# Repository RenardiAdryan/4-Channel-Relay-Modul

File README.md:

# 4-Channel-Relay-Modul
DIY Relay Modul

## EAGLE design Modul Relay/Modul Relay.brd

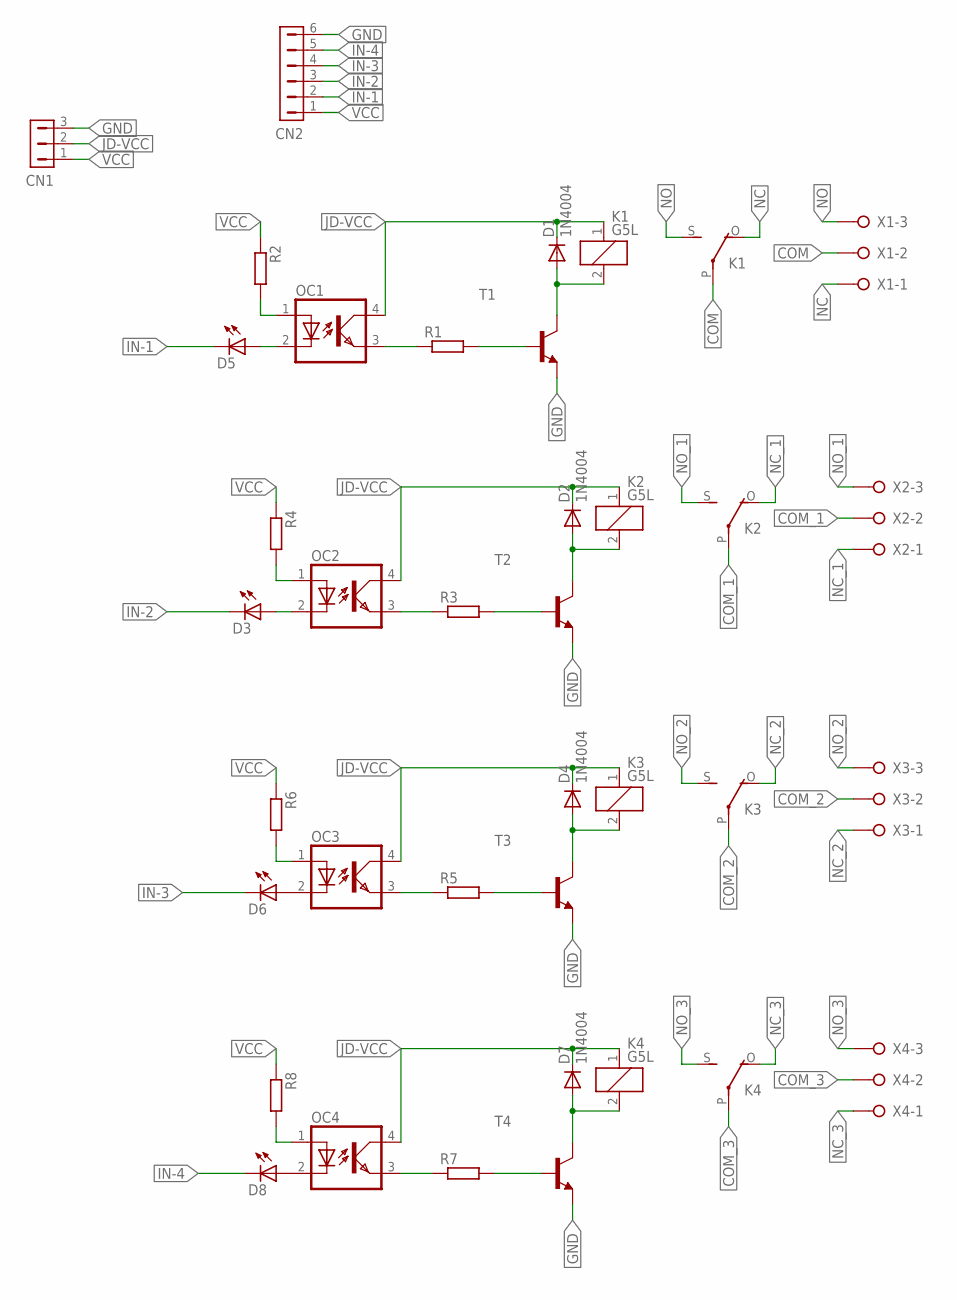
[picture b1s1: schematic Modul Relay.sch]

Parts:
CN1: HDR-1X3; SIP-100-3V
CN2: HDR-1X6-SIP-100; SIP-100-6V
D1, D2, D4, D7: 1N4004; DO41-10
D3, D5, D6, D8: LED3MM
K1, K2, K3, K4: G5L; G5LE
OC1, OC2, OC3, OC4: PC817; DIL04
R1, R2, R3, R4, R5, R6, R7, R8: R-EU_R0805; R0805
T1, T2, T3, T4: -NPN-TO92-ECB; TO92-ECB
X1, X2, X3, X4: W237-3E

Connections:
COM: K1.P, X1.2
COM_1: K2.P, X2.2
COM_2: K3.P, X3.2
COM_3: K4.P, X4.2
GND: CN1.3, CN2.6, T1.E, T2.E, T3.E, T4.E
IN-1: CN2.2, D5.K (C)
IN-2: CN2.3, D3.K (C)
IN-3: CN2.4, D6.K (C)
IN-4: CN2.5, D8.K (C)
JD-VCC: CN1.2, D1.C, D2.C, D4.C, D7.C, K1.1, K2.1, K3.1, K4.1, OC1.4 (COL), OC2.4 (COL), OC3.4 (COL), OC4.4 (COL)
unnamed: D2.A, K2.2, T2.C
unnamed: D1.A, K1.2, T1.C
unnamed: OC1.1 (A), R2.2
unnamed: R3.2, T2.B
unnamed: OC2.3 (EMIT), R3.1
unnamed: D3.A, OC2.2 (C)
unnamed: OC2.1 (A), R4.2
unnamed: D4.A, K3.2, T3.C
unnamed: R1.2, T1.B
unnamed: OC1.3 (EMIT), R1.1
unnamed: D5.A, OC1.2 (C)
unnamed: R5.2, T3.B
unnamed: OC3.3 (EMIT), R5.1
unnamed: D6.A, OC3.2 (C)
unnamed: OC3.1 (A), R6.2
unnamed: D7.A, K4.2, T4.C
unnamed: R7.2, T4.B
unnamed: OC4.3 (EMIT), R7.1
unnamed: D8.A, OC4.2 (C)
unnamed: OC4.1 (A), R8.2
NC: K1.O, X1.1
NC_1: K2.O, X2.1
NC_2: K3.O, X3.1
NC_3: K4.O, X4.1
NO: K1.S, X1.3
NO_1: K2.S, X2.3
NO_2: K3.S, X3.3
NO_3: K4.S, X4.3
VCC: CN1.1, CN2.1, R2.1, R4.1, R6.1, R8.1

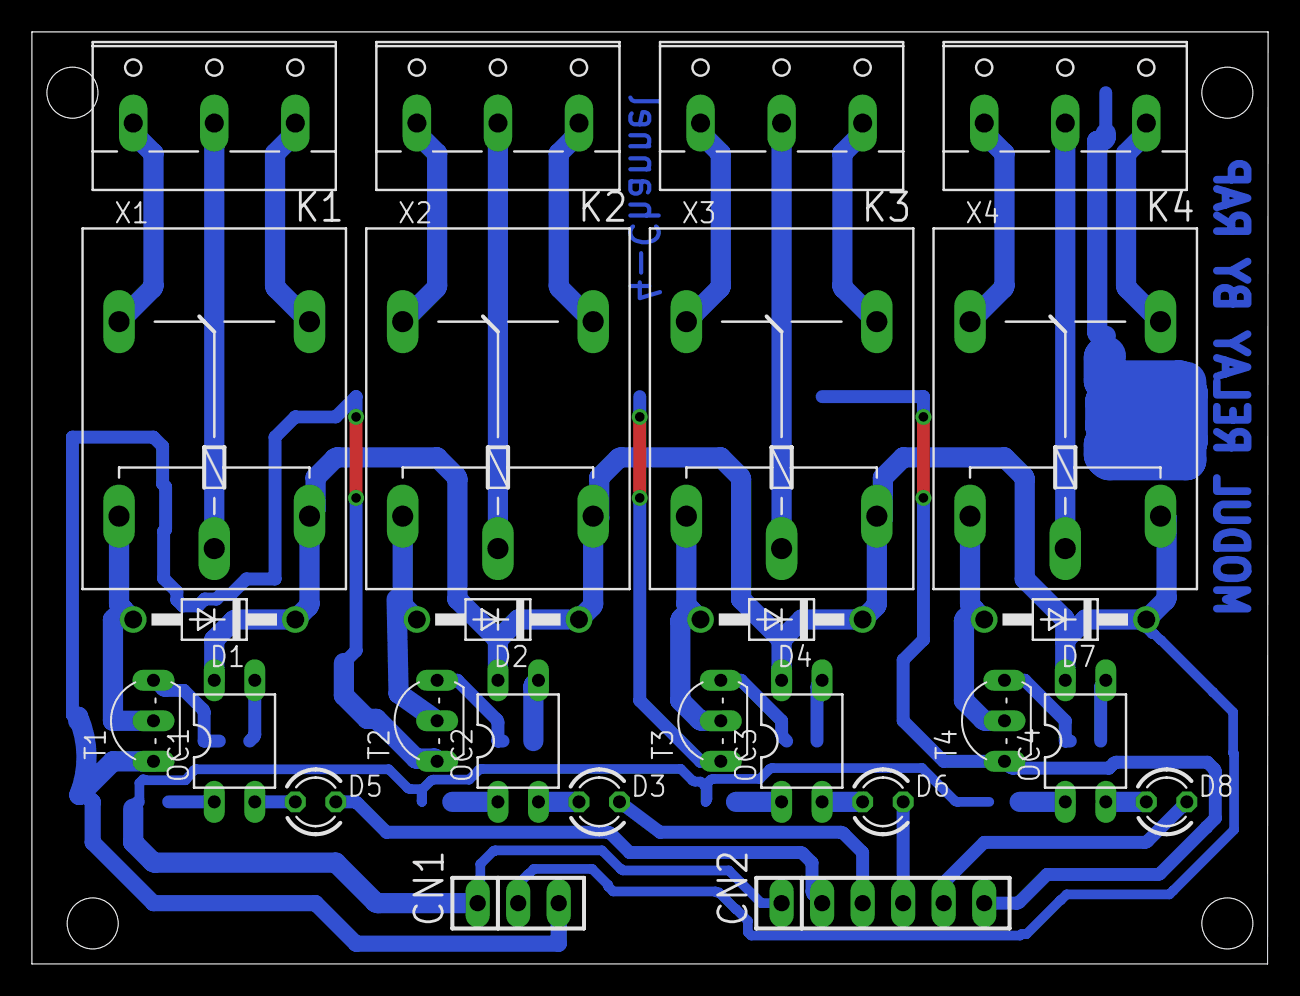
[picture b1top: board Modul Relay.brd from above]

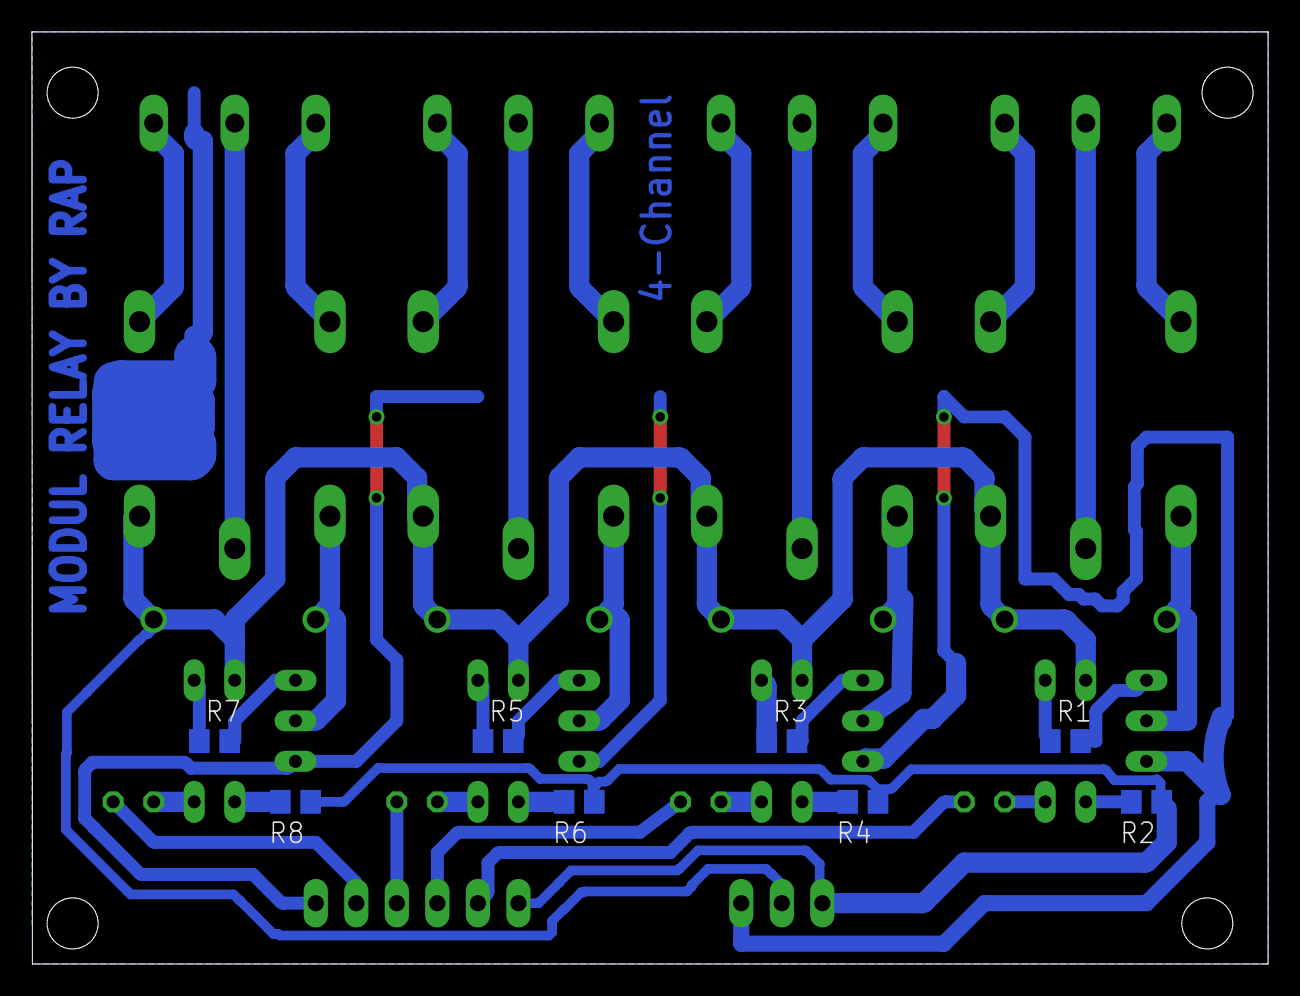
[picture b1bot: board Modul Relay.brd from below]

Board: 2 copper layers, 77.5 x 58.4 mm, 34 parts (8 on the bottom side), 39 nets.

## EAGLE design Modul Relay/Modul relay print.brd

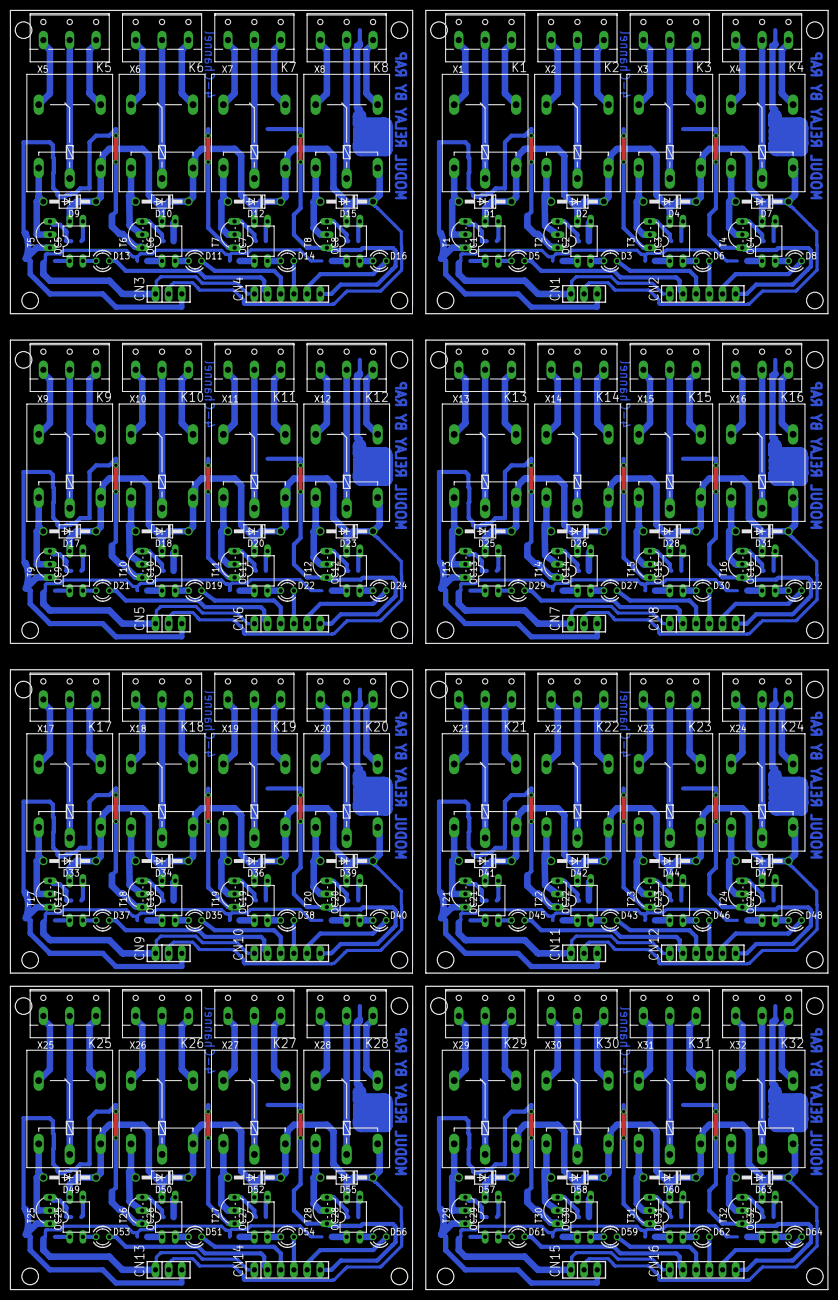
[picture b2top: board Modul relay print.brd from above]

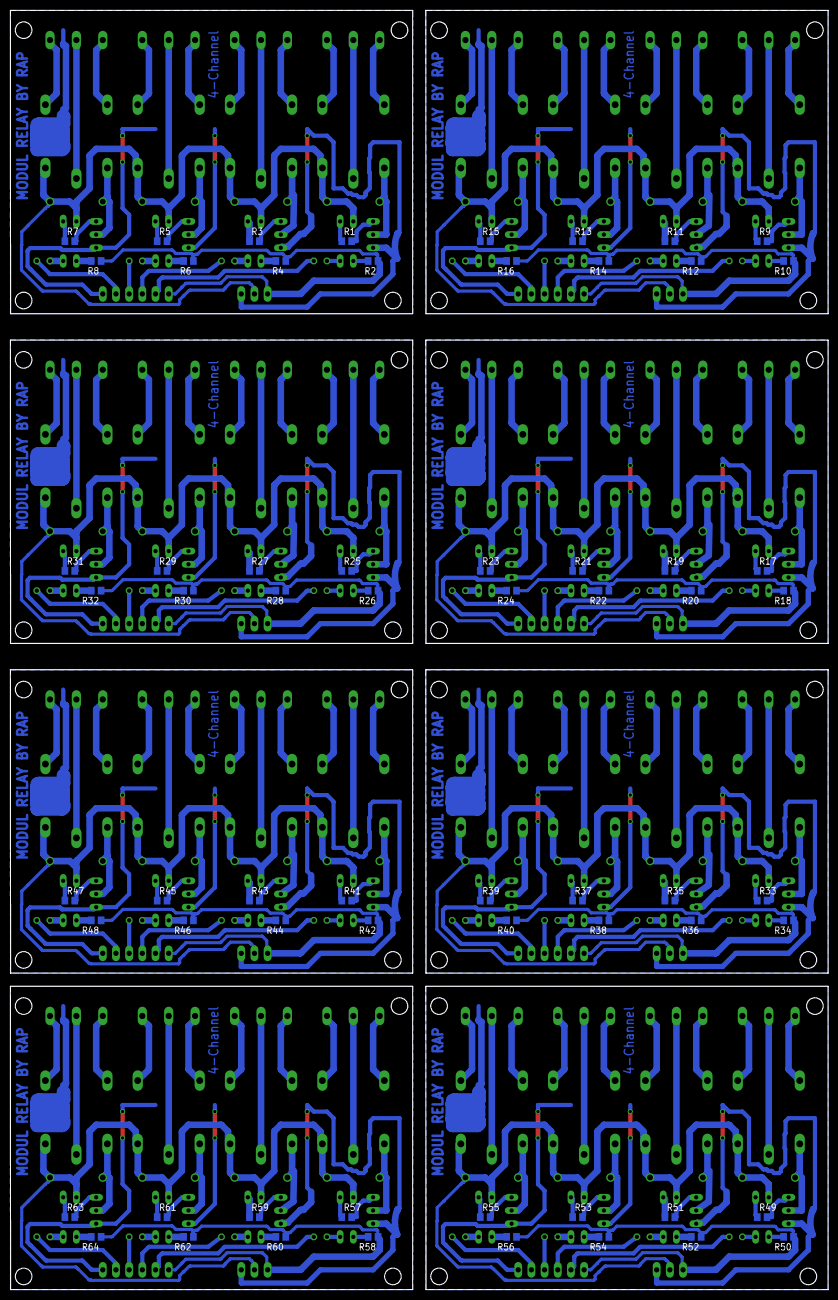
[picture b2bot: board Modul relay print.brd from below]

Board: 2 copper layers, 157.5 x 246.4 mm, 272 parts (64 on the bottom side), 312 nets.

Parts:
CN1, CN3, CN5, CN7, CN9, CN11, CN13, CN15: SIP-100-3V
CN2, CN4, CN6, CN8, CN10, CN12, CN14, CN16: SIP-100-6V
D1, D2, D4, D7, D9, D10, D12, D15, D17, D18, D20, D23, D25, D26, D28, D31, D33, D34, D36, D39, D41, D42, D44, D47, D49, D50, D52, D55, D57, D58, D60, D63: 1N4004; DO41-10
D3, D5, D6, D8, D11, D13, D14, D16, D19, D21, D22, D24, D27, D29, D30, D32, D35, D37, D38, D40, D43, D45, D46, D48, D51, D53, D54, D56, D59, D61, D62, D64: LED3MM
K1, K2, K3, K4, K5, K6, K7, K8, K9, K10, K11, K12, K13, K14, K15, K16, K17, K18, K19, K20, K21, K22, K23, K24, K25, K26, K27, K28, K29, K30, K31, K32: G5L; G5LE
OC1, OC2, OC3, OC4, OC5, OC6, OC7, OC8, OC9, OC10, OC11, OC12, OC13, OC14, OC15, OC16, OC17, OC18, OC19, OC20, OC21, OC22, OC23, OC24, OC25, OC26, OC27, OC28, OC29, OC30, OC31, OC32: DIL04
R1, R2, R3, R4, R5, R6, R7, R8, R9, R10, R11, R12, R13, R14, R15, R16, R17, R18, R19, R20, R21, R22, R23, R24, R25, R26, R27, R28, R29, R30, R31, R32, R33, R34, R35, R36, R37, R38, R39, R40, R41, R42, R43, R44, R45, R46, R47, R48, R49, R50, R51, R52, R53, R54, R55, R56, R57, R58, R59, R60, R61, R62, R63, R64: R0805
T1, T2, T3, T4, T5, T6, T7, T8, T9, T10, T11, T12, T13, T14, T15, T16, T17, T18, T19, T20, T21, T22, T23, T24, T25, T26, T27, T28, T29, T30, T31, T32: TO92-ECB
X1, X2, X3, X4, X5, X6, X7, X8, X9, X10, X11, X12, X13, X14, X15, X16, X17, X18, X19, X20, X21, X22, X23, X24, X25, X26, X27, X28, X29, X30, X31, X32: W237-3E

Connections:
COM: K1.P, X1.2
COM1: K5.P, X5.2
COM2: K9.P, X9.2
COM3: K13.P, X13.2
COM4: K17.P, X17.2
COM5: K21.P, X21.2
COM6: K25.P, X25.2
COM7: K29.P, X29.2
COM_1: K2.P, X2.2
COM_2: K3.P, X3.2
COM_3: K4.P, X4.2
COM_4: K6.P, X6.2
COM_5: K7.P, X7.2
COM_6: K8.P, X8.2
COM_7: K10.P, X10.2
COM_8: K11.P, X11.2
COM_9: K12.P, X12.2
COM_10: K14.P, X14.2
COM_11: K15.P, X15.2
COM_12: K16.P, X16.2
COM_13: K18.P, X18.2
COM_14: K19.P, X19.2
COM_15: K20.P, X20.2
COM_16: K22.P, X22.2
COM_17: K23.P, X23.2
COM_18: K24.P, X24.2
COM_19: K26.P, X26.2
COM_20: K27.P, X27.2
COM_21: K28.P, X28.2
COM_22: K30.P, X30.2
COM_23: K31.P, X31.2
COM_24: K32.P, X32.2
GND: CN1.3, CN2.6, T1.E, T2.E, T3.E, T4.E
GND1: CN3.3, CN4.6, T5.E, T6.E, T7.E, T8.E
GND2: CN5.3, CN6.6, T9.E, T10.E, T11.E, T12.E
GND3: CN7.3, CN8.6, T13.E, T14.E, T15.E, T16.E
GND4: CN9.3, CN10.6, T17.E, T18.E, T19.E, T20.E
GND5: CN11.3, CN12.6, T21.E, T22.E, T23.E, T24.E
GND6: CN13.3, CN14.6, T25.E, T26.E, T27.E, T28.E
GND7: CN15.3, CN16.6, T29.E, T30.E, T31.E, T32.E
IN-1: CN2.2, D5.K
IN-2: CN2.3, D3.K
IN-3: CN2.4, D6.K
IN-4: CN2.5, D8.K
IN-5: CN4.2, D13.K
IN-6: CN4.3, D11.K
IN-7: CN4.4, D14.K
IN-8: CN4.5, D16.K
IN-9: CN6.2, D21.K
IN-10: CN6.3, D19.K
IN-11: CN6.4, D22.K
IN-12: CN6.5, D24.K
IN-13: CN8.2, D29.K
IN-14: CN8.3, D27.K
IN-15: CN8.4, D30.K
IN-16: CN8.5, D32.K
IN-17: CN10.2, D37.K
IN-18: CN10.3, D35.K
IN-19: CN10.4, D38.K
IN-20: CN10.5, D40.K
IN-21: CN12.2, D45.K
IN-22: CN12.3, D43.K
IN-23: CN12.4, D46.K
IN-24: CN12.5, D48.K
IN-25: CN14.2, D53.K
IN-26: CN14.3, D51.K
IN-27: CN14.4, D54.K
IN-28: CN14.5, D56.K
IN-29: CN16.2, D61.K
IN-30: CN16.3, D59.K
IN-31: CN16.4, D62.K
IN-32: CN16.5, D64.K
JD-VCC: CN1.2, D1.C, D2.C, D4.C, D7.C, K1.1, K2.1, K3.1, K4.1, OC1.4, OC2.4, OC3.4, OC4.4
JD-VCC1: CN3.2, D9.C, D10.C, D12.C, D15.C, K5.1, K6.1, K7.1, K8.1, OC5.4, OC6.4, OC7.4, OC8.4
JD-VCC2: CN5.2, D17.C, D18.C, D20.C, D23.C, K9.1, K10.1, K11.1, K12.1, OC9.4, OC10.4, OC11.4, OC12.4
JD-VCC3: CN7.2, D25.C, D26.C, D28.C, D31.C, K13.1, K14.1, K15.1, K16.1, OC13.4, OC14.4, OC15.4, OC16.4
JD-VCC4: CN9.2, D33.C, D34.C, D36.C, D39.C, K17.1, K18.1, K19.1, K20.1, OC17.4, OC18.4, OC19.4, OC20.4
JD-VCC5: CN11.2, D41.C, D42.C, D44.C, D47.C, K21.1, K22.1, K23.1, K24.1, OC21.4, OC22.4, OC23.4, OC24.4
JD-VCC6: CN13.2, D49.C, D50.C, D52.C, D55.C, K25.1, K26.1, K27.1, K28.1, OC25.4, OC26.4, OC27.4, OC28.4
JD-VCC7: CN15.2, D57.C, D58.C, D60.C, D63.C, K29.1, K30.1, K31.1, K32.1, OC29.4, OC30.4, OC31.4, OC32.4
unnamed: D2.A, K2.2, T2.C
unnamed: D1.A, K1.2, T1.C
unnamed: OC1.1, R2.2
unnamed: R3.2, T2.B
unnamed: OC2.3, R3.1
unnamed: D3.A, OC2.2
unnamed: OC2.1, R4.2
unnamed: D4.A, K3.2, T3.C
unnamed: R1.2, T1.B
unnamed: OC1.3, R1.1
unnamed: D5.A, OC1.2
unnamed: R5.2, T3.B
unnamed: OC3.3, R5.1
unnamed: D6.A, OC3.2
unnamed: OC3.1, R6.2
unnamed: D7.A, K4.2, T4.C
unnamed: R7.2, T4.B
unnamed: OC4.3, R7.1
unnamed: D8.A, OC4.2
unnamed: OC4.1, R8.2
unnamed: D9.A, K5.2, T5.C
unnamed: R9.2, T5.B
unnamed: OC5.3, R9.1
unnamed: D13.A, OC5.2
unnamed: OC5.1, R10.2
unnamed: D10.A, K6.2, T6.C
unnamed: R11.2, T6.B
unnamed: OC6.3, R11.1
unnamed: D11.A, OC6.2
unnamed: OC6.1, R12.2
unnamed: D12.A, K7.2, T7.C
unnamed: R13.2, T7.B
unnamed: OC7.3, R13.1
unnamed: D14.A, OC7.2
unnamed: OC7.1, R14.2
unnamed: D15.A, K8.2, T8.C
unnamed: R15.2, T8.B
unnamed: OC8.3, R15.1
unnamed: D16.A, OC8.2
unnamed: OC8.1, R16.2
unnamed: D17.A, K9.2, T9.C
unnamed: R17.2, T9.B
unnamed: OC9.3, R17.1
unnamed: D21.A, OC9.2
unnamed: OC9.1, R18.2
unnamed: D18.A, K10.2, T10.C
unnamed: R19.2, T10.B
unnamed: OC10.3, R19.1
unnamed: D19.A, OC10.2
unnamed: OC10.1, R20.2
unnamed: D20.A, K11.2, T11.C
unnamed: R21.2, T11.B
unnamed: OC11.3, R21.1
unnamed: D22.A, OC11.2
unnamed: OC11.1, R22.2
unnamed: D23.A, K12.2, T12.C
unnamed: R23.2, T12.B
unnamed: OC12.3, R23.1
unnamed: D24.A, OC12.2
unnamed: OC12.1, R24.2
unnamed: D25.A, K13.2, T13.C
unnamed: R25.2, T13.B
unnamed: OC13.3, R25.1
unnamed: D29.A, OC13.2
unnamed: OC13.1, R26.2
unnamed: D26.A, K14.2, T14.C
unnamed: R27.2, T14.B
unnamed: OC14.3, R27.1
unnamed: D27.A, OC14.2
unnamed: OC14.1, R28.2
unnamed: D28.A, K15.2, T15.C
unnamed: R29.2, T15.B
unnamed: OC15.3, R29.1
unnamed: D30.A, OC15.2
unnamed: OC15.1, R30.2
unnamed: D31.A, K16.2, T16.C
unnamed: R31.2, T16.B
unnamed: OC16.3, R31.1
unnamed: D32.A, OC16.2
unnamed: OC16.1, R32.2
unnamed: D33.A, K17.2, T17.C
unnamed: R33.2, T17.B
unnamed: OC17.3, R33.1
unnamed: D37.A, OC17.2
unnamed: OC17.1, R34.2
unnamed: D34.A, K18.2, T18.C
unnamed: R35.2, T18.B
unnamed: OC18.3, R35.1
unnamed: D35.A, OC18.2
unnamed: OC18.1, R36.2
unnamed: D36.A, K19.2, T19.C
unnamed: R37.2, T19.B
unnamed: OC19.3, R37.1
unnamed: D38.A, OC19.2
unnamed: OC19.1, R38.2
unnamed: D39.A, K20.2, T20.C
unnamed: R39.2, T20.B
unnamed: OC20.3, R39.1
unnamed: D40.A, OC20.2
unnamed: OC20.1, R40.2
unnamed: D41.A, K21.2, T21.C
unnamed: R41.2, T21.B
unnamed: OC21.3, R41.1
unnamed: D45.A, OC21.2
unnamed: OC21.1, R42.2
unnamed: D42.A, K22.2, T22.C
unnamed: R43.2, T22.B
unnamed: OC22.3, R43.1
unnamed: D43.A, OC22.2
unnamed: OC22.1, R44.2
unnamed: D44.A, K23.2, T23.C
unnamed: R45.2, T23.B
unnamed: OC23.3, R45.1
unnamed: D46.A, OC23.2
unnamed: OC23.1, R46.2
unnamed: D47.A, K24.2, T24.C
unnamed: R47.2, T24.B
unnamed: OC24.3, R47.1
unnamed: D48.A, OC24.2
unnamed: OC24.1, R48.2
unnamed: D49.A, K25.2, T25.C
unnamed: R49.2, T25.B
unnamed: OC25.3, R49.1
unnamed: D53.A, OC25.2
unnamed: OC25.1, R50.2
unnamed: D50.A, K26.2, T26.C
unnamed: R51.2, T26.B
unnamed: OC26.3, R51.1
unnamed: D51.A, OC26.2
unnamed: OC26.1, R52.2
unnamed: D52.A, K27.2, T27.C
unnamed: R53.2, T27.B
unnamed: OC27.3, R53.1
unnamed: D54.A, OC27.2
unnamed: OC27.1, R54.2
unnamed: D55.A, K28.2, T28.C
unnamed: R55.2, T28.B
unnamed: OC28.3, R55.1
unnamed: D56.A, OC28.2
unnamed: OC28.1, R56.2
unnamed: D57.A, K29.2, T29.C
unnamed: R57.2, T29.B
unnamed: OC29.3, R57.1
unnamed: D61.A, OC29.2
unnamed: OC29.1, R58.2
unnamed: D58.A, K30.2, T30.C
unnamed: R59.2, T30.B
unnamed: OC30.3, R59.1
unnamed: D59.A, OC30.2
unnamed: OC30.1, R60.2
unnamed: D60.A, K31.2, T31.C
unnamed: R61.2, T31.B
unnamed: OC31.3, R61.1
unnamed: D62.A, OC31.2
unnamed: OC31.1, R62.2
unnamed: D63.A, K32.2, T32.C
unnamed: R63.2, T32.B
unnamed: OC32.3, R63.1
unnamed: D64.A, OC32.2
unnamed: OC32.1, R64.2
NC: K1.O, X1.1
NC1: K5.O, X5.1
NC2: K9.O, X9.1
NC3: K13.O, X13.1
NC4: K17.O, X17.1
NC5: K21.O, X21.1
NC6: K25.O, X25.1
NC7: K29.O, X29.1
NC_1: K2.O, X2.1
NC_2: K3.O, X3.1
NC_3: K4.O, X4.1
NC_4: K6.O, X6.1
NC_5: K7.O, X7.1
NC_6: K8.O, X8.1
NC_7: K10.O, X10.1
NC_8: K11.O, X11.1
NC_9: K12.O, X12.1
NC_10: K14.O, X14.1
NC_11: K15.O, X15.1
NC_12: K16.O, X16.1
NC_13: K18.O, X18.1
NC_14: K19.O, X19.1
NC_15: K20.O, X20.1
NC_16: K22.O, X22.1
NC_17: K23.O, X23.1
NC_18: K24.O, X24.1
NC_19: K26.O, X26.1
NC_20: K27.O, X27.1
NC_21: K28.O, X28.1
NC_22: K30.O, X30.1
NC_23: K31.O, X31.1
NC_24: K32.O, X32.1
NO: K1.S, X1.3
NO1: K5.S, X5.3
NO2: K9.S, X9.3
NO3: K13.S, X13.3
NO4: K17.S, X17.3
NO5: K21.S, X21.3
NO6: K25.S, X25.3
NO7: K29.S, X29.3
NO_1: K2.S, X2.3
NO_2: K3.S, X3.3
NO_3: K4.S, X4.3
NO_4: K6.S, X6.3
NO_5: K7.S, X7.3
NO_6: K8.S, X8.3
NO_7: K10.S, X10.3
NO_8: K11.S, X11.3
NO_9: K12.S, X12.3
NO_10: K14.S, X14.3
NO_11: K15.S, X15.3
NO_12: K16.S, X16.3
NO_13: K18.S, X18.3
NO_14: K19.S, X19.3
NO_15: K20.S, X20.3
NO_16: K22.S, X22.3
NO_17: K23.S, X23.3
NO_18: K24.S, X24.3
NO_19: K26.S, X26.3
NO_20: K27.S, X27.3
NO_21: K28.S, X28.3
NO_22: K30.S, X30.3
NO_23: K31.S, X31.3
NO_24: K32.S, X32.3
VCC: CN1.1, CN2.1, R2.1, R4.1, R6.1, R8.1
VCC1: CN3.1, CN4.1, R10.1, R12.1, R14.1, R16.1
VCC2: CN5.1, CN6.1, R18.1, R20.1, R22.1, R24.1
VCC3: CN7.1, CN8.1, R26.1, R28.1, R30.1, R32.1
VCC4: CN9.1, CN10.1, R34.1, R36.1, R38.1, R40.1
VCC5: CN11.1, CN12.1, R42.1, R44.1, R46.1, R48.1
VCC6: CN13.1, CN14.1, R50.1, R52.1, R54.1, R56.1
VCC7: CN15.1, CN16.1, R58.1, R60.1, R62.1, R64.1

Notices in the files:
parts and their libraries:
con-hdrs40: Copyright (C) 2004, Bob Starr (bobstarr@mindspring.com)
